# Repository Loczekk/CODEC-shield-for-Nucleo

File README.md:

# CODEC-shield-for-Nucleo

First version of codec shield for Nucleo STM32L476

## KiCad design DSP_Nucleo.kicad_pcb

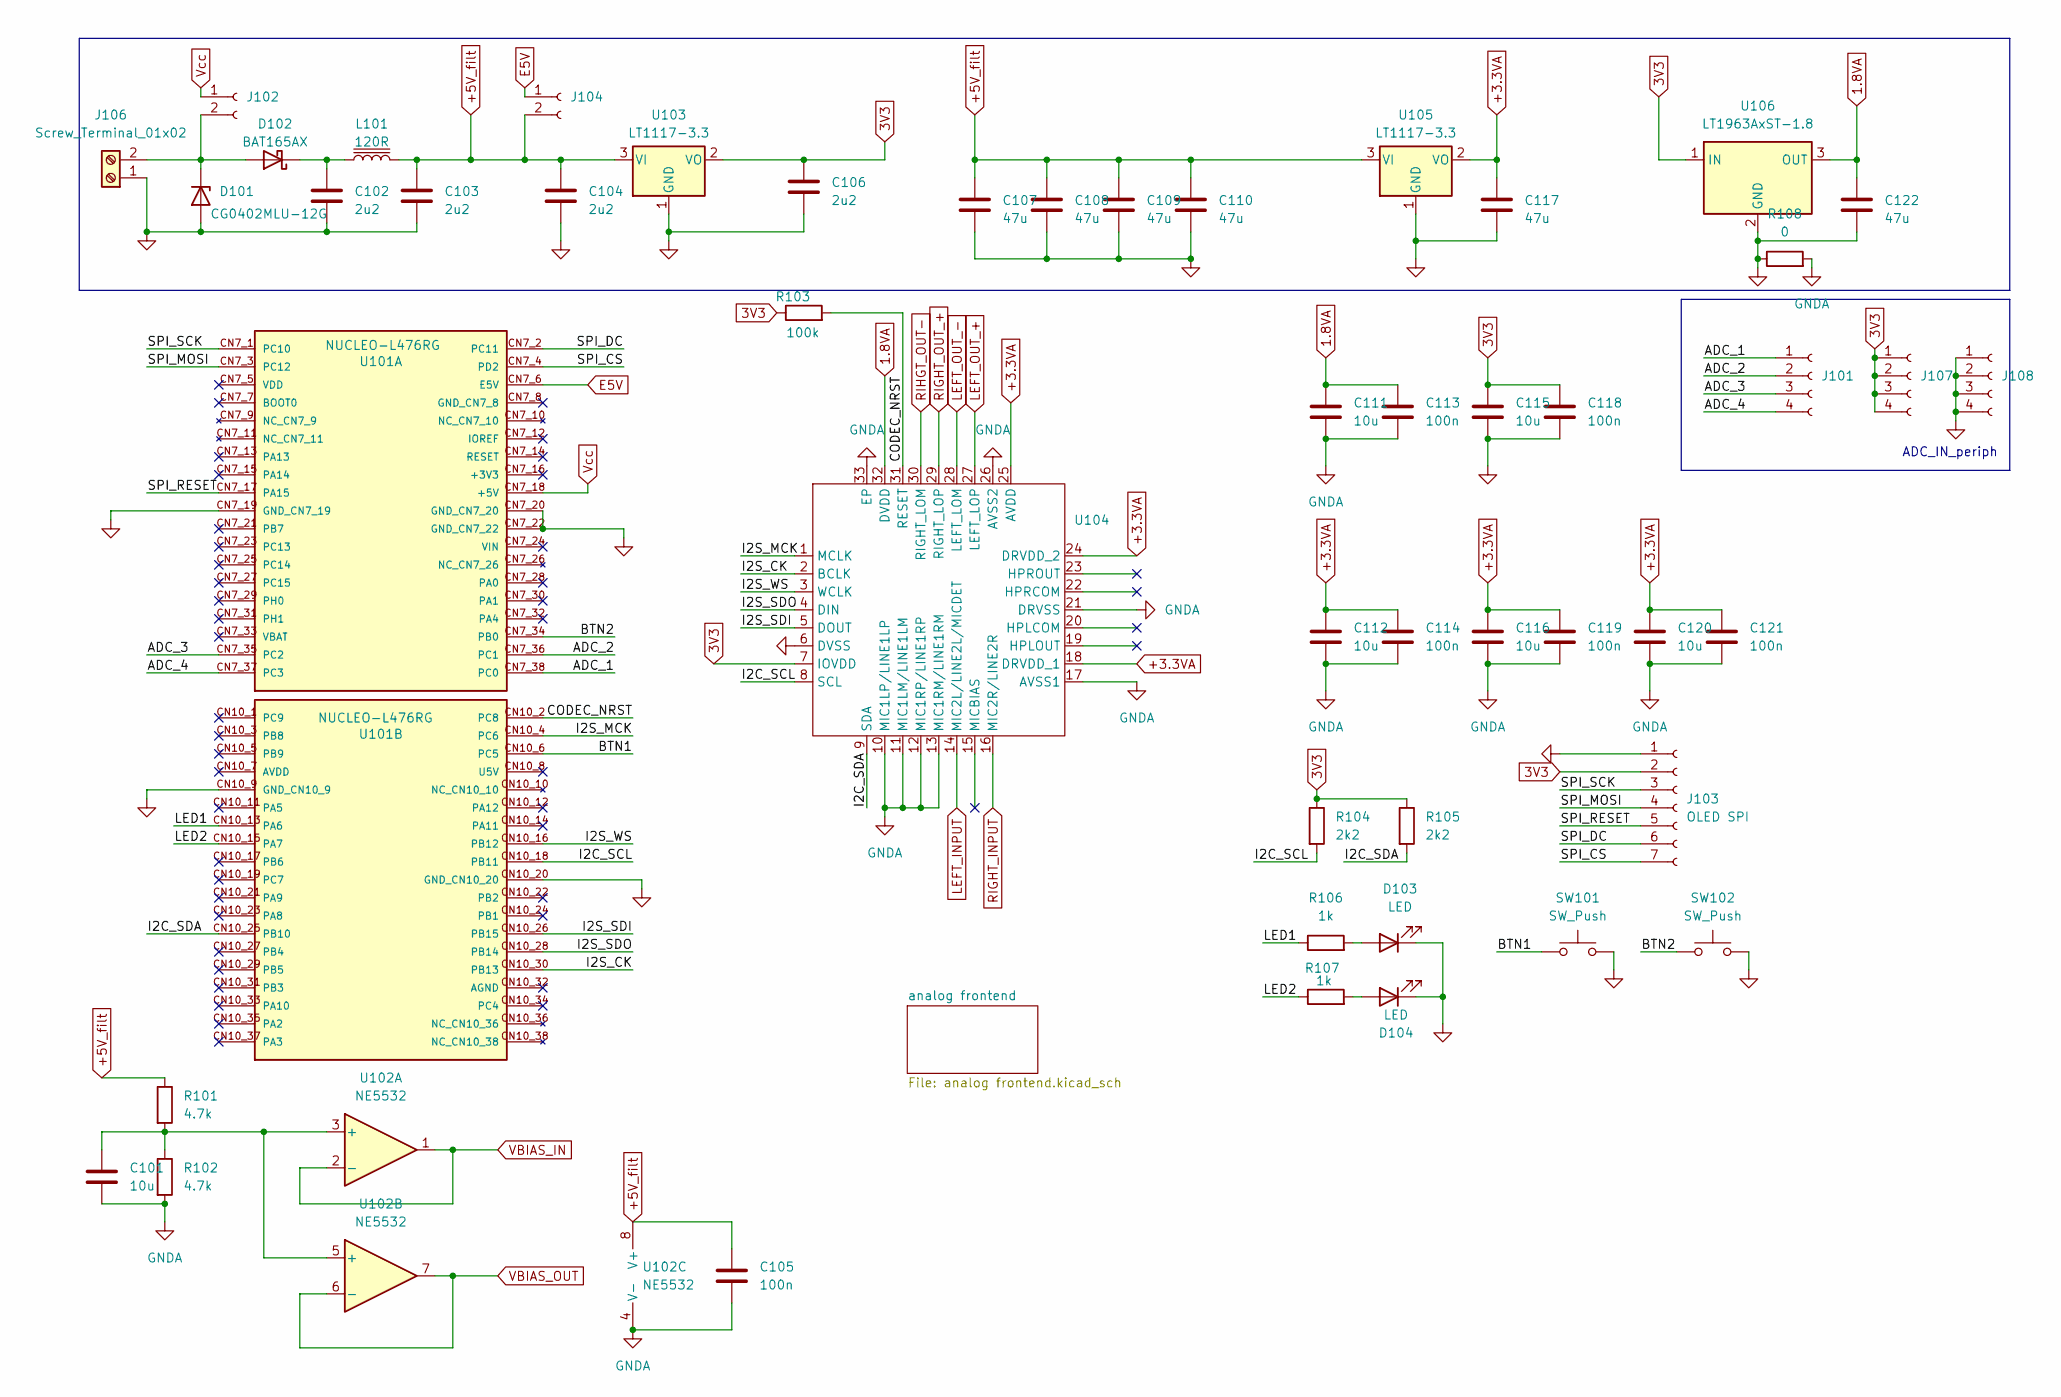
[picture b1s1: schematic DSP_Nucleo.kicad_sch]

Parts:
C101, C111, C112, C115, C116, C120: 10u; C_0603_1608Metric
C102, C103, C104, C106: 2u2; C_0402_1005Metric
C105, C113, C114, C118, C119, C121: 100n; C_0402_1005Metric
C107, C108, C109, C110, C117, C122: 47u; C_1210_3225Metric
D101: CG0402MLU-12G; D_SOD-523
D102: BAT165AX; D_SOD-323
D103, D104: LED; LED_0805_2012Metric
J101, J107, J108: Conn_01x04_Socket; PinSocket_1x04_P2.54mm_Vertical
J102, J104: Conn_01x02_Socket; PinHeader_1x02_P2.54mm_Vertical
J103: OLED SPI; PinHeader_1x07_P2.54mm_Vertical
J106: Screw_Terminal_01x02; BarrelJack_CUI_PJ-063AH_Horizontal
L101: 120R; C_0603_1608Metric
R101, R102: 4.7k; C_0402_1005Metric
R103: 100k; C_0402_1005Metric
R104, R105: 2k2; R_0402_1005Metric
R106, R107: 1k; R_0402_1005Metric
R108: 0; R_0402_1005Metric
SW101, SW102: SW_Push; SW_Tactile_SPST_NO_Straight_CK_PTS636Sx25SMTRLFS
U101: NUCLEO-L476RG; MODULE_NUCLEO-L476RG; PARTREV 15
U102: NE5532; SOIC-8_3.9x4.9mm_P1.27mm
U103, U105: LT1117-3.3; SOT-223-3_TabPin2
U104: VQFN-32-1EP_5x5mm_P0.5mm_EP3.1x3.1mm
U106: LT1963AxST-1.8; SOT-223-3_TabPin2

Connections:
1.8VA: C111.1, C113.1, C122.1, U104.32 (DVDD), U106.3 (OUT)
3V3: C106.1, C115.1, C118.1, J103.2, J107.1, J107.2, J107.3, J107.4, R103.1, R104.1, R105.1, U103.2 (VO), U104.7 (IOVDD), U106.1 (IN)
+3.3VA: C112.1, C114.1, C116.1, C117.1, C119.1, C120.1, C121.1, U104.18 (DRVDD_1), U104.24 (DRVDD_2), U104.25 (AVDD), U105.2 (VO)
+5V_filt: C103.2, C104.1, C105.1, C107.1, C108.1, C109.1, C110.1, J104.2, L101.2, R101.1, U102.8 (V+), U103.3 (VI), U105.3 (VI); also elsewhere on the board
/ADC_1: J101.1, U101.CN7_38 (PC0)
/ADC_2: J101.2, U101.CN7_36 (PC1)
/ADC_3: J101.3, U101.CN7_35 (PC2)
/ADC_4: J101.4, U101.CN7_37 (PC3)
/BTN1: SW101.1, U101.CN10_6 (PC5)
/BTN2: SW102.1, U101.CN7_34 (PB0)
/CODEC_NRST: R103.2, U101.CN10_2 (PC8), U104.31 (RESET)
/I2C_SCL: R104.2, U101.CN10_18 (PB11), U104.8 (SCL)
/I2C_SDA: R105.2, U101.CN10_25 (PB10), U104.9 (SDA)
/I2S_CK: U101.CN10_30 (PB13), U104.2 (BCLK)
/I2S_MCK: U101.CN10_4 (PC6), U104.1 (MCLK)
/I2S_SDI: U101.CN10_26 (PB15), U104.5 (DOUT)
/I2S_SDO: U101.CN10_28 (PB14), U104.4 (DIN)
/I2S_WS: U101.CN10_16 (PB12), U104.3 (WCLK)
/LED1: R106.1, U101.CN10_13 (PA6)
/LED2: R107.1, U101.CN10_15 (PA7)
/SPI_CS: J103.7, U101.CN7_4 (PD2)
/SPI_DC: J103.6, U101.CN7_2 (PC11)
/SPI_MOSI: J103.4, U101.CN7_3 (PC12)
/SPI_RESET: J103.5, U101.CN7_17 (PA15)
/SPI_SCK: J103.3, U101.CN7_1 (PC10)
E5V: J104.1, U101.CN7_6 (E5V); also elsewhere on the board
GND: C102.1, C103.1, C104.2, C106.2, C107.2, C108.2, C109.2, C110.2, C115.2, C117.2, C118.2, C122.2, D101.2 (A), D103.1 (K), D104.1 (K), J103.1, J106.1, J108.1, J108.2, J108.3, J108.4, R108.1, SW101.2, SW102.2, U101.CN7_19 (GND_CN7_19), U101.CN7_20 (GND_CN7_20), U101.CN7_22 (GND_CN7_22), U101.CN10_9 (GND_CN10_9), U101.CN10_20 (GND_CN10_20), U103.1 (GND), U104.6 (DVSS), U105.1 (GND), U106.2 (GND); also elsewhere on the board
GNDA: C101.2, C105.2, C111.2, C112.2, C113.2, C114.2, C116.2, C119.2, C120.2, C121.2, R102.2, R108.2, U102.4 (V-), U104.10 (MIC1LP/LINE1LP), U104.11 (MIC1LM/LINE1LM), U104.12 (MIC1RP/LINE1RP), U104.13 (MIC1RM/LINE1RM), U104.17 (AVSS1), U104.21 (DRVSS), U104.26 (AVSS2), U104.33 (EP); also elsewhere on the board
LEFT_INPUT: U104.14 (MIC2L/LINE2L/MICDET); also elsewhere on the board
LEFT_OUT_+: U104.27 (LEFT_LOP); also elsewhere on the board
LEFT_OUT_-: U104.28 (LEFT_LOM); also elsewhere on the board
unnamed: D101.1 (K), D102.2 (A), J102.2, J106.2
unnamed: C102.2, D102.1 (K), L101.1
unnamed: D103.2 (A), R106.2
unnamed: D104.2 (A), R107.2
unnamed: C101.1, R101.2, R102.1, U102.3 (+), U102.5 (+)
RIGHT_INPUT: U104.16 (MIC2R/LINE2R); also elsewhere on the board
RIGHT_OUT_+: U104.29 (RIGHT_LOP); also elsewhere on the board
RIHGT_OUT-: U104.30 (RIGHT_LOM); also elsewhere on the board
VBIAS_IN: U102.1, U102.2 (-); also elsewhere on the board
VBIAS_OUT: U102.6 (-), U102.7; also elsewhere on the board
Vcc: J102.1, U101.CN7_18 (+5V)

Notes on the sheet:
ADC_IN_periph

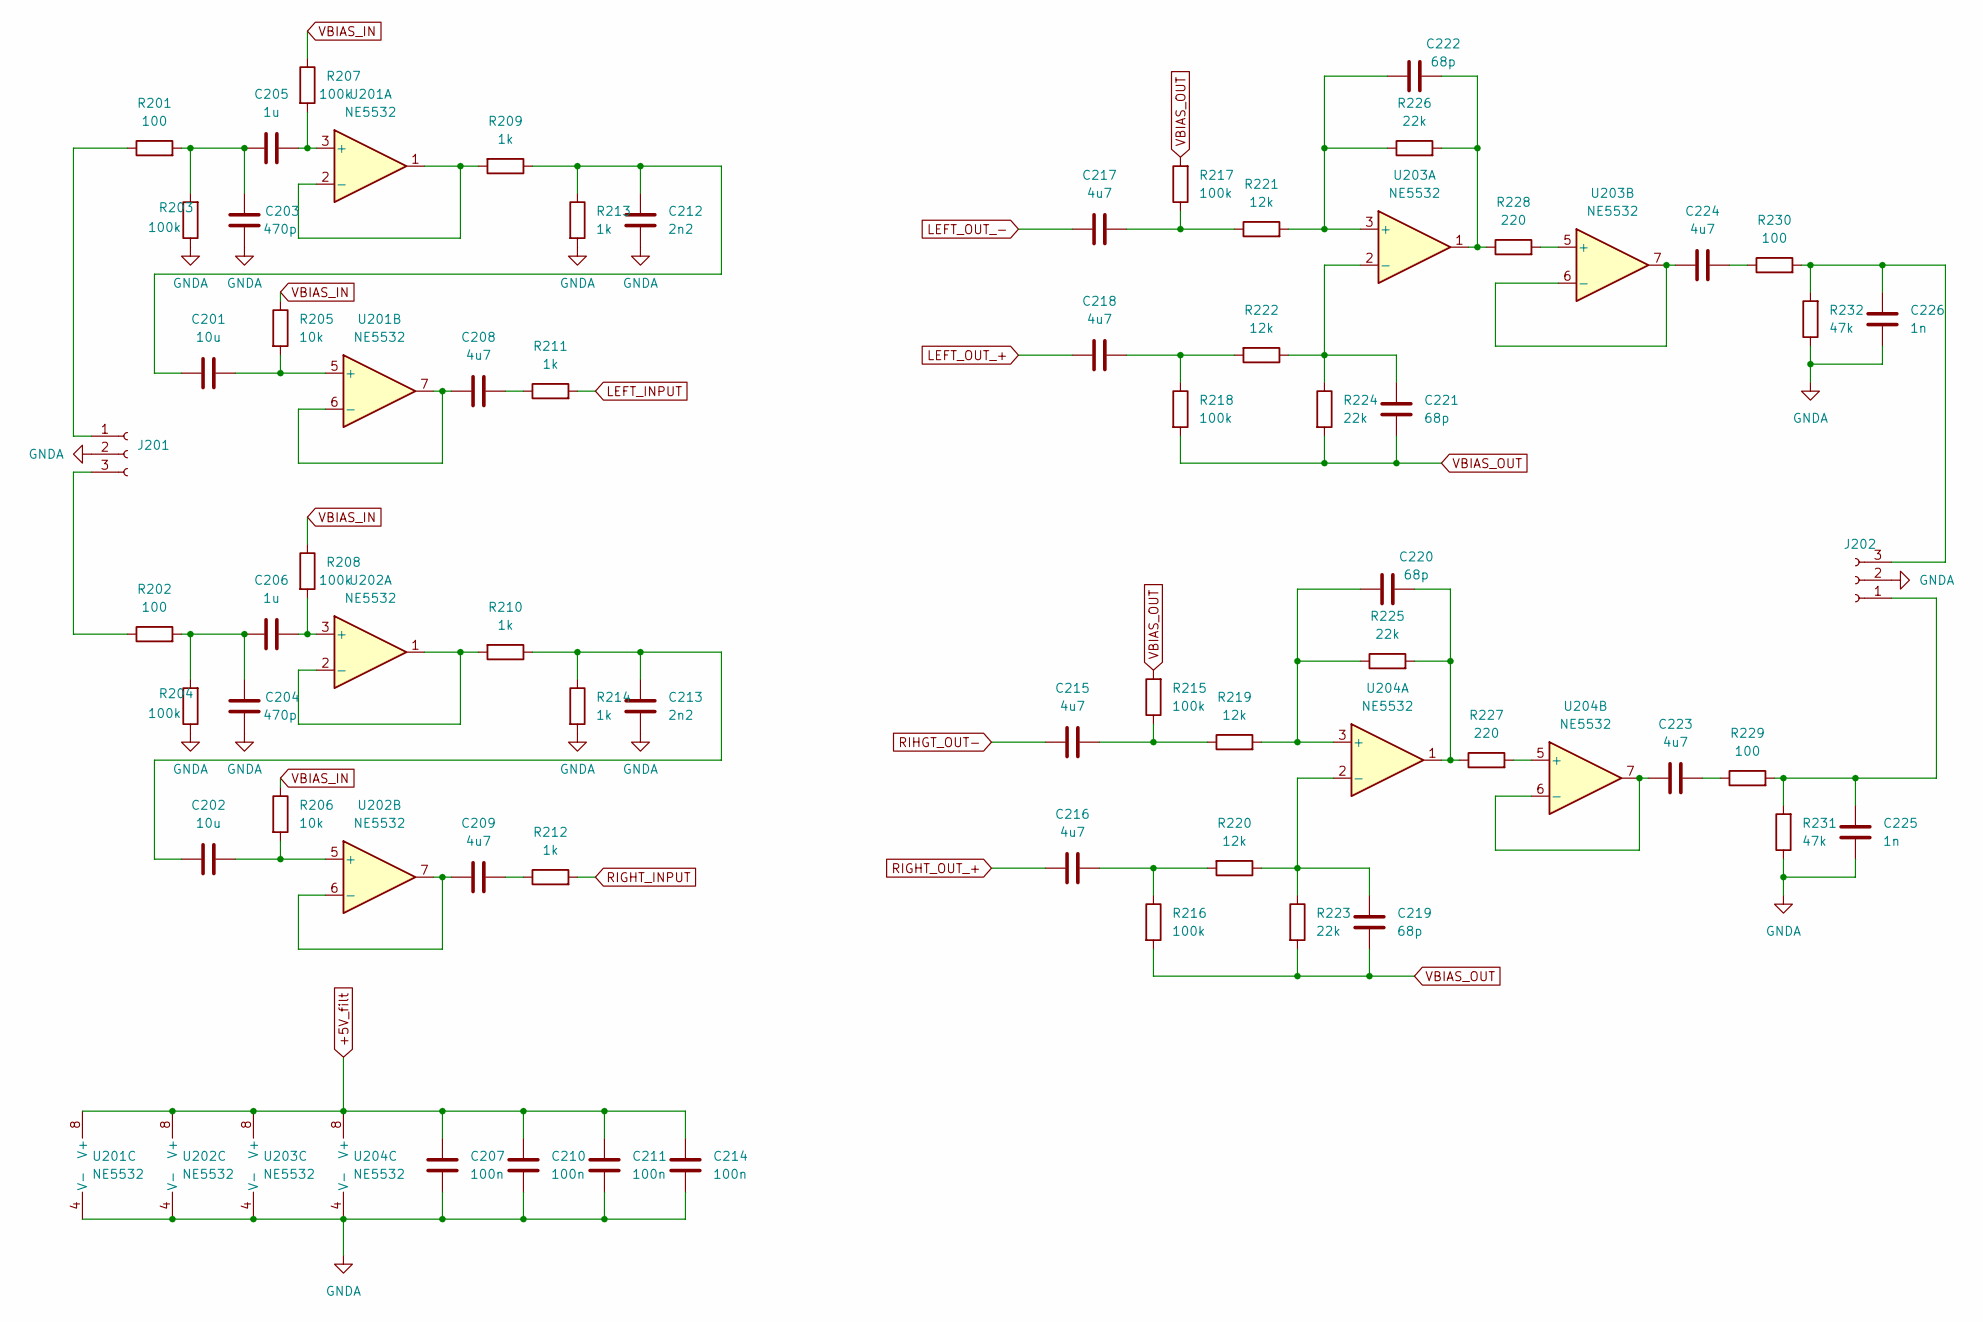
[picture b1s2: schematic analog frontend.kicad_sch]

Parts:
C201, C202: 10u; C_0603_1608Metric
C203, C204: 470p; C_0402_1005Metric
C205, C206: 1u; C_0402_1005Metric
C207, C210, C211, C214: 100n; C_0402_1005Metric
C208, C209, C215, C216, C217, C218, C223, C224: 4u7; C_0402_1005Metric
C212, C213: 2n2; C_0402_1005Metric
C219, C220, C221, C222: 68p; C_0402_1005Metric
C225, C226: 1n; C_0402_1005Metric
J201, J202: Conn_01x03_Socket; Jack_3.5mm_Ledino_KB3SPRS_Horizontal
R201, R202, R229, R230: 100; C_0402_1005Metric
R203, R204, R207, R208, R215, R216, R217, R218: 100k; C_0402_1005Metric
R205, R206: 10k; C_0402_1005Metric
R209, R210, R211, R212, R213, R214: 1k; C_0402_1005Metric
R219, R220, R221, R222: 12k; C_0402_1005Metric
R223, R224, R225, R226: 22k; C_0402_1005Metric
R227, R228: 220; C_0402_1005Metric
R231, R232: 47k; C_0402_1005Metric
U201, U202, U203, U204: NE5532; SOIC-8_3.9x4.9mm_P1.27mm

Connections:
+5V_filt: C207.1, C210.1, C211.1, C214.1, U201.8 (V+), U202.8 (V+), U203.8 (V+), U204.8 (V+); also elsewhere on the board
GNDA: C203.2, C204.2, C207.2, C210.2, C211.2, C212.1, C213.1, C214.2, C225.2, C226.2, J201.2, J202.2, R203.1, R204.1, R213.2, R214.2, R231.1, R232.1, U201.4 (V-), U202.4 (V-), U203.4 (V-), U204.4 (V-); also elsewhere on the board
LEFT_INPUT: R211.2; also elsewhere on the board
LEFT_OUT_+: C218.1; also elsewhere on the board
LEFT_OUT_-: C217.1; also elsewhere on the board
unnamed: C201.2, C212.2, R209.1, R213.1
unnamed: C202.2, C213.2, R210.1, R214.1
unnamed: C203.1, C205.1, R201.2, R203.2
unnamed: C204.1, C206.1, R202.2, R204.2
unnamed: C208.1, R211.1
unnamed: C209.1, R212.1
unnamed: C215.2, R215.1, R219.1
unnamed: C216.2, R216.1, R220.2
unnamed: C217.2, R217.1, R221.1
unnamed: C218.2, R218.1, R222.2
unnamed: C220.2, R225.2, R227.1, U204.1
unnamed: C222.2, R226.2, R228.1, U203.1
unnamed: C223.1, R229.1
unnamed: C224.1, R230.1
unnamed: J201.1, R201.1
unnamed: J201.3, R202.1
unnamed: C225.1, J202.1, R229.2, R231.2
unnamed: C226.1, J202.3, R230.2, R232.2
unnamed: C205.2, R207.2, U201.3 (+)
unnamed: R209.2, U201.1, U201.2 (-)
unnamed: C201.1, R205.2, U201.5 (+)
unnamed: C208.2, U201.6 (-), U201.7
unnamed: C206.2, R208.2, U202.3 (+)
unnamed: R210.2, U202.1, U202.2 (-)
unnamed: C202.1, R206.2, U202.5 (+)
unnamed: C209.2, U202.6 (-), U202.7
unnamed: C222.1, R221.2, R226.1, U203.3 (+)
unnamed: C221.2, R222.1, R224.1, U203.2 (-)
unnamed: R228.2, U203.5 (+)
unnamed: C224.2, U203.6 (-), U203.7
unnamed: C220.1, R219.2, R225.1, U204.3 (+)
unnamed: C219.2, R220.1, R223.1, U204.2 (-)
unnamed: R227.2, U204.5 (+)
unnamed: C223.2, U204.6 (-), U204.7
RIGHT_INPUT: R212.2; also elsewhere on the board
RIGHT_OUT_+: C216.1; also elsewhere on the board
RIHGT_OUT-: C215.1; also elsewhere on the board
VBIAS_IN: R205.1, R206.1, R207.1, R208.1; also elsewhere on the board
VBIAS_OUT: C219.1, C221.1, R215.2, R216.2, R217.2, R218.2, R223.2, R224.2; also elsewhere on the board

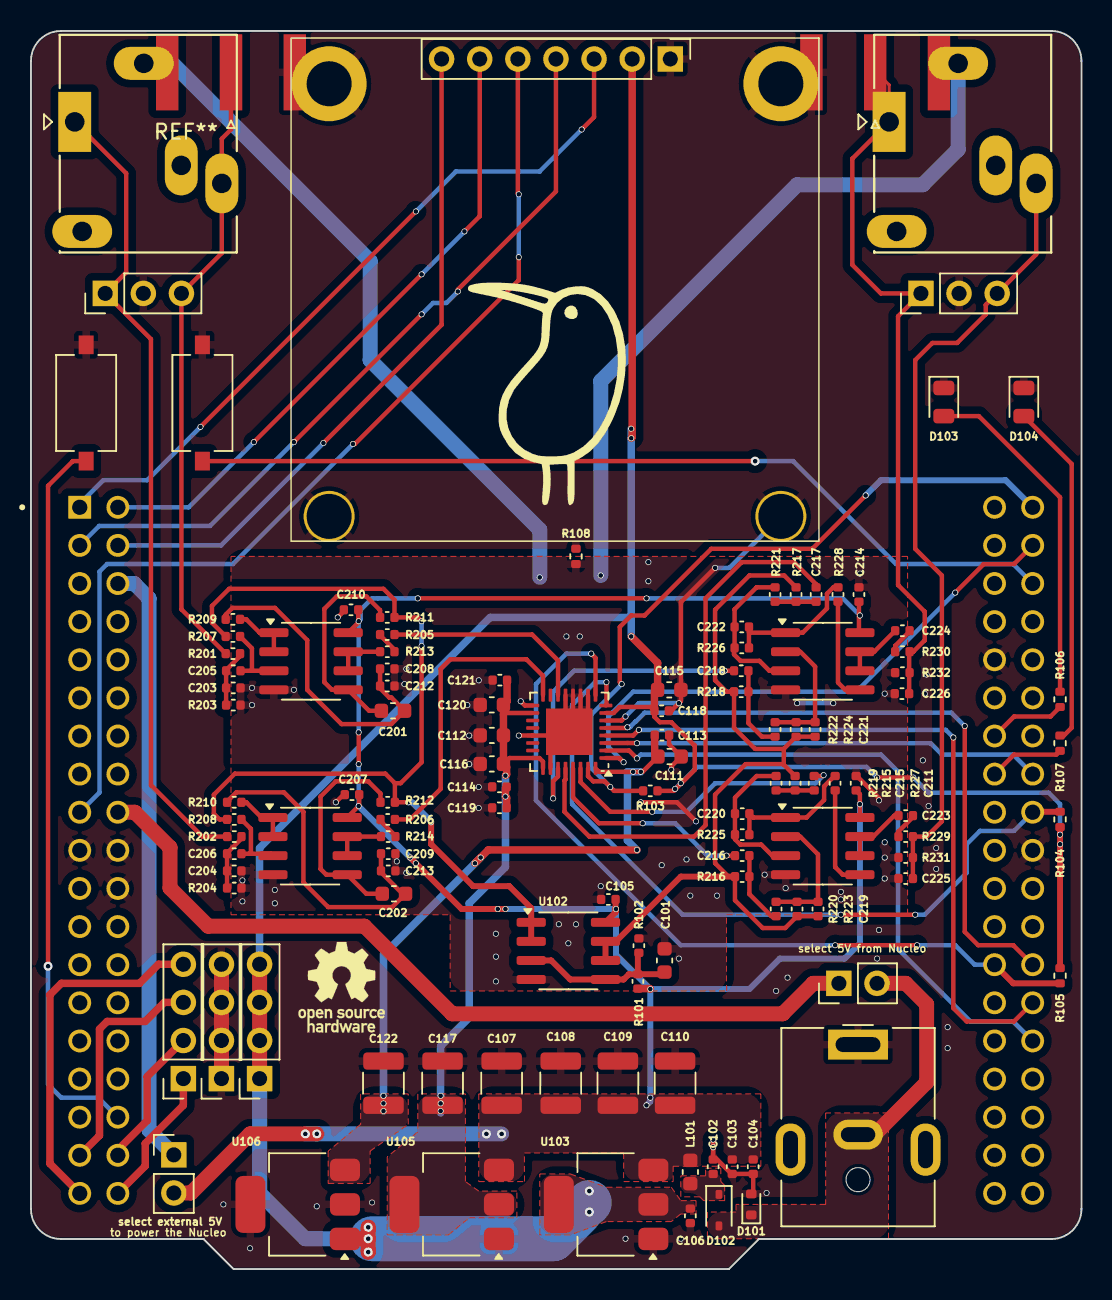
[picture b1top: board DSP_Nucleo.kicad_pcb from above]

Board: 2 copper layers, 70.0 x 82.5 mm, 115 parts (1 on the bottom side), 76 nets.

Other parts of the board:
R108#2: 0; R_0402_1005Metric
select external 5V : Conn_01x02_Socket; PinHeader_1x02_P2.54mm_Vertical

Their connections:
+5V_filt: select external 5V.2; also elsewhere on the board
E5V: select external 5V.1; also elsewhere on the board
GND: R108#2.1; also elsewhere on the board
GNDA: R108#2.2; also elsewhere on the board
